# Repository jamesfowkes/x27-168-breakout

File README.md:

# x27-168-breakout
PCB and control software for an X27-168 stepper

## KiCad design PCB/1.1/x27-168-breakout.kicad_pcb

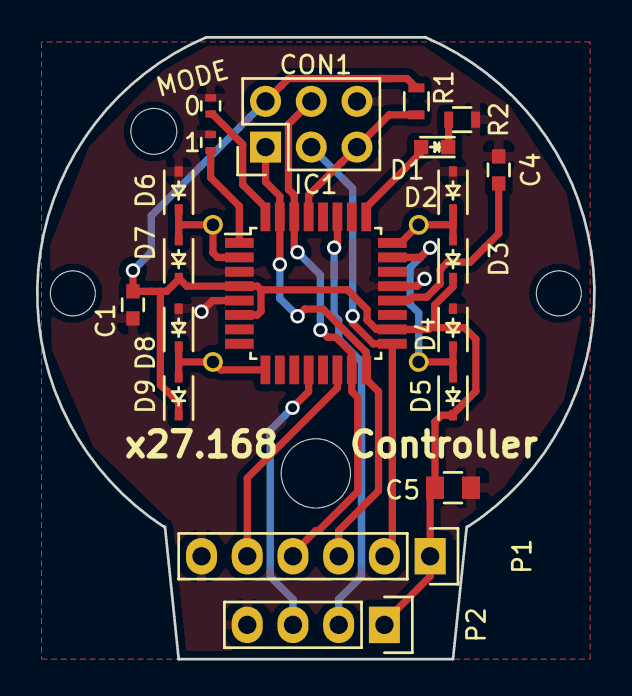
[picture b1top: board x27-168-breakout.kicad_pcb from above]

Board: 2 copper layers, 30.9 x 34.5 mm, 21 parts (1 on the bottom side), 18 nets.

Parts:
C1, C4: 100n; C_0603
C5: 10u; C_0805
CON1: AVR-ISP-6; Pin_Header_Straight_2x03
D1: RED; LED_0603
D2, D3, D4, D5, D6, D7, D8, D9: LL4148; SOD-323
IC1: ATMEGA328P-A; TQFP-32_7x7mm_Pitch0.8mm
JP1, JP2: DNP; R_0402
M1: x27.168
P1: COMMS; Pin_Header_Straight_1x06
P2: SIGNALS; Pin_Header_Straight_1x04
R1: 10K; R_0603
R2: 1K; R_0603

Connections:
/ANALOG_IN: IC1.27, P2.2
/M1: D8.1, D9.2, IC1.9, M1.1A
/M2: D6.1, D7.2, IC1.2, M1.1B
/M3: D4.1, D5.2, IC1.23, M1.2A
/M4: D2.1, D3.2, IC1.24, M1.2B
/MISO: CON1.1, IC1.16, IC1.31, P1.3
/MODE0: IC1.32, JP2.1
/MODE1: IC1.1, JP1.1
/MOSI: CON1.4, IC1.15, IC1.30, P1.4
/PWM_IN: IC1.12, P2.3
/SCK: CON1.3, IC1.17, P1.2
/~RST: CON1.5, IC1.29, R1.2
/~SS: IC1.14, P1.5
GND: C1.2, C4.2, C5.2, CON1.6, D2.2, D4.2, D6.2, D8.2, IC1.3, IC1.5, IC1.21, JP1.2, JP2.2, P1.6, P2.4, R2.2
unnamed: C4.1, IC1.20
unnamed: D1.1, R2.1
unnamed: D1.2, IC1.25
VCC: C1.1, C5.1, CON1.2, D3.1, D5.1, D7.1, D9.1, IC1.4, IC1.6, IC1.18, P1.1, P2.1, R1.1

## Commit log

2016-06-15 Untested modules and ino file
2016-06-15 First PCB revision
2016-06-15 Added PWM module to sandbox
2016-06-17 Began work on stepper control
2016-06-17 Compiles under arduino
2016-06-17 Moved M3 to correct pin
2016-07-02 Fixed path issues
2016-07-03 Changed from c++ to c, added makefile
2016-07-31 Latest sandbox (build not working)
2016-07-31 Fixed --gc-sections build issue
2016-08-02 Fixed incorrect mode selection
2016-08-03 Fixed libraries
2016-08-03 Fixed mode selection issue
2016-08-03 Fixed incorrect F_CPU in build file
2016-08-09 Fixed step bitmask error
2016-08-09 Added PDF of schematic version 1.0
2016-08-10 Added motor test mode
